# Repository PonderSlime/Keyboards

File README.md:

# Keyboards

A collection of all my personal keyboard projects.

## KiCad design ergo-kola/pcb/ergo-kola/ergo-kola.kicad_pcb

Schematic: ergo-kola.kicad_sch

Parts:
C1, C2, C3, C4, C5, C6, C7, C8, C9, C10, C11, C12, C13, C14, C15, C16, C17, C18, C19, C20, C21, C22, C23, C24, C25, C26, C27, C28, C29, C30, C31, C32, C33, C34, C35, C36, C37, C38, C39, C40, C41, C42, C43, C44, C45, C46, C47, C48, C49, C50, C51, C52: C 100uf; C_0805_2012Metric_Pad1.18x1.45mm_HandSolder
D1, D2, D3, D4, D5, D6, D7, D8, D9, D10, D11, D12, D13, D14, D15, D16, D17, D18, D19, D20, D21, D22, D23, D24, D25, D26, D27, D28, D29, D30, D31, D32, D33, D34, D35, D36, D37, D38, D39, D40, D41, D42, D43, D44, D45, D46, D47, D48, D49, D50, D51, D52: D; D_SOD-123
J1, J2: L_TRRS; PJ-320A
L1, L2, L3, L4, L5, L6, L7, L8, L9, L10, L11, L12, L13, L14, L15, L16, L17, L18, L19, L20, L21, L22, L23, L24, L25, L26, L27, L28, L29, L30, L31, L32, L33, L34, L35, L36, L37, L38, L39, L40, L41, L42, L43, L44, L45, L46, L47, L48, L49, L50, L51, L52: WS2812B; SK6812-MINI-E
SW1, SW2, SW3, SW4, SW5, SW6, SW7, SW8, SW9, SW10, SW11, SW12, SW13, SW14, SW15, SW16, SW17, SW18, SW19, SW20, SW21, SW22, SW23, SW24, SW25, SW26, SW27, SW28, SW29, SW30, SW31, SW32, SW33, SW34, SW35, SW36, SW37, SW38, SW39, SW40, SW41, SW42, SW43, SW44, SW45, SW46, SW47, SW48, SW49, SW50, SW51, SW52: CherryMX; CherryMX_1.00u_PCB_KailhSocket
U1, U2: Pico; RPi_Pico_SMD_TH

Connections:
GND: J1.1 (S), J2.1 (S), L1.3 (VSS), L2.3 (VSS), L3.3 (VSS), L4.3 (VSS), L5.3 (VSS), L6.3 (VSS), L7.3 (VSS), L8.3 (VSS), L9.3 (VSS), L10.3 (VSS), L11.3 (VSS), L12.3 (VSS), L13.3 (VSS), L14.3 (VSS), L15.3 (VSS), L16.3 (VSS), L17.3 (VSS), L18.3 (VSS), L19.3 (VSS), L20.3 (VSS), L21.3 (VSS), L22.3 (VSS), L23.3 (VSS), L24.3 (VSS), L25.3 (VSS), L26.3 (VSS), L27.3 (VSS), L28.3 (VSS), L29.3 (VSS), L30.3 (VSS), L31.3 (VSS), L32.3 (VSS), L33.3 (VSS), L34.3 (VSS), L35.3 (VSS), L36.3 (VSS), L37.3 (VSS), L38.3 (VSS), L39.3 (VSS), L40.3 (VSS), L41.3 (VSS), L42.3 (VSS), L43.3 (VSS), L44.3 (VSS), L45.3 (VSS), L46.3 (VSS), L47.3 (VSS), L48.3 (VSS), L49.3 (VSS), L50.3 (VSS), L51.3 (VSS), L52.3 (VSS), U1.3 (GND), U1.8 (GND), U1.13 (GND), U1.18 (GND), U1.23 (GND), U1.28 (GND), U1.38 (GND), U1.42 (GND), U2.3 (GND), U2.8 (GND), U2.13 (GND), U2.18 (GND), U2.23 (GND), U2.28 (GND), U2.38 (GND), U2.42 (GND)
L_C0: SW1.1, SW11.1, SW25.1, SW37.1, U1.10 (GPIO7)
L_C1: SW5.1, SW17.1, SW29.1, SW41.1, U1.11 (GPIO8)
L_C2: SW3.1, SW13.1, SW23.1, SW35.1, U1.12 (GPIO9)
L_C3: SW7.1, SW15.1, SW27.1, SW39.1, U1.14 (GPIO10)
L_C4: SW9.1, SW21.1, SW33.1, SW45.1, SW49.1, U1.15 (GPIO11)
L_C5: SW19.1, SW31.1, SW43.1, SW47.1, SW51.1, U1.16 (GPIO12)
L_R0: D1.1 (K), D3.1 (K), D5.1 (K), D7.1 (K), D9.1 (K), D19.1 (K), U1.27 (GPIO21)
L_R1: D11.1 (K), D13.1 (K), D15.1 (K), D17.1 (K), D21.1 (K), D31.1 (K), U1.26 (GPIO20)
L_R2: D23.1 (K), D25.1 (K), D27.1 (K), D29.1 (K), D33.1 (K), D43.1 (K), U1.25 (GPIO19)
L_R3: D35.1 (K), D37.1 (K), D39.1 (K), D41.1 (K), D45.1 (K), D47.1 (K), U1.24 (GPIO18)
L_R4: D49.1 (K), D51.1 (K), U1.22 (GPIO17)
L_RGB: L1.4 (DIN), U1.1 (GPIO0)
L_RX: J1.3 (R1), U1.7 (GPIO5_(RX))
L_TX: J1.4 (R2), U1.6 (GPIO4_(TX))
L_VBUS: C1.1, C11.1, C25.1, C37.1, C49.1, J1.2 (T), U1.40 (VBUS)
unnamed: D1.2 (A), SW1.2
unnamed: D2.2 (A), SW2.2
unnamed: D3.2 (A), SW3.2
unnamed: D4.2 (A), SW4.2
unnamed: D5.2 (A), SW5.2
unnamed: D6.2 (A), SW6.2
unnamed: D7.2 (A), SW7.2
unnamed: D8.2 (A), SW8.2
unnamed: D9.2 (A), SW9.2
unnamed: D10.2 (A), SW10.2
unnamed: D11.2 (A), SW11.2
unnamed: D12.2 (A), SW12.2
unnamed: D13.2 (A), SW13.2
unnamed: D14.2 (A), SW14.2
unnamed: D15.2 (A), SW15.2
unnamed: D16.2 (A), SW16.2
unnamed: D17.2 (A), SW17.2
unnamed: D18.2 (A), SW18.2
unnamed: D19.2 (A), SW19.2
unnamed: D20.2 (A), SW20.2
unnamed: D21.2 (A), SW21.2
unnamed: D22.2 (A), SW22.2
unnamed: D23.2 (A), SW23.2
unnamed: D24.2 (A), SW24.2
unnamed: D25.2 (A), SW25.2
unnamed: D26.2 (A), SW26.2
unnamed: D27.2 (A), SW27.2
unnamed: D28.2 (A), SW28.2
unnamed: D29.2 (A), SW29.2
unnamed: D30.2 (A), SW30.2
unnamed: D31.2 (A), SW31.2
unnamed: D32.2 (A), SW32.2
unnamed: D33.2 (A), SW33.2
unnamed: D34.2 (A), SW34.2
unnamed: D35.2 (A), SW35.2
unnamed: D36.2 (A), SW36.2
unnamed: D37.2 (A), SW37.2
unnamed: D38.2 (A), SW38.2
unnamed: D39.2 (A), SW39.2
unnamed: D40.2 (A), SW40.2
unnamed: D41.2 (A), SW41.2
unnamed: D42.2 (A), SW42.2
unnamed: D43.2 (A), SW43.2
unnamed: D44.2 (A), SW44.2
unnamed: D45.2 (A), SW45.2
unnamed: D46.2 (A), SW46.2
unnamed: D47.2 (A), SW47.2
unnamed: D48.2 (A), SW48.2
unnamed: D49.2 (A), SW49.2
unnamed: D50.2 (A), SW50.2
unnamed: D51.2 (A), SW51.2
unnamed: D52.2 (A), SW52.2
unnamed: L1.2 (DOUT), L5.4 (DIN)
unnamed: C1.2, C5.1, L1.1 (VDD)
unnamed: L2.4 (DIN), L6.2 (DOUT)
unnamed: L2.2 (DOUT), L32.4 (DIN)
unnamed: C2.2, L2.1 (VDD)
unnamed: L3.4 (DIN), L5.2 (DOUT)
unnamed: L3.2 (DOUT), L7.4 (DIN)
unnamed: C3.2, C7.1, L3.1 (VDD)
unnamed: L4.4 (DIN), L8.2 (DOUT)
unnamed: L4.2 (DOUT), L6.4 (DIN)
unnamed: C4.2, C6.1, L4.1 (VDD)
unnamed: C3.1, C5.2, L5.1 (VDD)
unnamed: C2.1, C6.2, L6.1 (VDD)
unnamed: L7.2 (DOUT), L9.4 (DIN)
unnamed: C7.2, C9.1, L7.1 (VDD)
unnamed: C4.1, C8.2, L8.1 (VDD)
unnamed: C9.2, C19.1, L9.1 (VDD)
unnamed: L10.4 (DIN), L20.2 (DOUT)
unnamed: L8.4 (DIN), L10.2 (DOUT)
unnamed: C8.1, C10.2, L10.1 (VDD)
unnamed: L11.4 (DIN), L19.2 (DOUT)
unnamed: L11.2 (DOUT), L17.4 (DIN)
unnamed: C11.2, C17.1, L11.1 (VDD)
unnamed: L12.4 (DIN), L18.2 (DOUT)
unnamed: L12.2 (DOUT), L44.4 (DIN)
unnamed: C12.2, L12.1 (VDD)
unnamed: L13.4 (DIN), L17.2 (DOUT)
unnamed: L13.2 (DOUT), L15.4 (DIN)
unnamed: C13.2, C15.1, L13.1 (VDD)
unnamed: L14.4 (DIN), L16.2 (DOUT)
unnamed: L14.2 (DOUT), L18.4 (DIN)
unnamed: C14.2, C18.1, L14.1 (VDD)
unnamed: L15.2 (DOUT), L21.4 (DIN)
unnamed: C15.2, C21.1, L15.1 (VDD)
unnamed: L16.4 (DIN), L22.2 (DOUT)
unnamed: C14.1, C16.2, L16.1 (VDD)
unnamed: C13.1, C17.2, L17.1 (VDD)
unnamed: C12.1, C18.2, L18.1 (VDD)
unnamed: L9.2 (DOUT), L19.4 (DIN)
unnamed: C19.2, L19.1 (VDD)
unnamed: C10.1, C20.2, L20.1 (VDD)
unnamed: L21.2 (DOUT), L31.4 (DIN)
unnamed: C21.2, C31.1, L21.1 (VDD)
unnamed: L22.4 (DIN), L32.2 (DOUT)
unnamed: C16.1, C22.2, L22.1 (VDD)
unnamed: L23.4 (DIN), L29.2 (DOUT)
unnamed: L23.2 (DOUT), L27.4 (DIN)
unnamed: C23.2, C27.1, L23.1 (VDD)
unnamed: L24.4 (DIN), L28.2 (DOUT)
unnamed: L24.2 (DOUT), L30.4 (DIN)
unnamed: C24.2, C30.1, L24.1 (VDD)
unnamed: L25.4 (DIN), L31.2 (DOUT)
unnamed: L25.2 (DOUT), L29.4 (DIN)
unnamed: C25.2, C29.1, L25.1 (VDD)
unnamed: L26.4 (DIN), L30.2 (DOUT)
unnamed: L26.2 (DOUT), L48.4 (DIN)
unnamed: C26.2, L26.1 (VDD)
unnamed: L27.2 (DOUT), L33.4 (DIN)
unnamed: C27.2, C33.1, L27.1 (VDD)
unnamed: L28.4 (DIN), L34.2 (DOUT)
unnamed: C24.1, C28.2, L28.1 (VDD)
unnamed: C23.1, C29.2, L29.1 (VDD)
unnamed: C26.1, C30.2, L30.1 (VDD)
unnamed: C31.2, L31.1 (VDD)
unnamed: C22.1, C32.2, L32.1 (VDD)
unnamed: L33.2 (DOUT), L43.4 (DIN)
unnamed: C33.2, C43.1, L33.1 (VDD)
unnamed: L34.4 (DIN), L44.2 (DOUT)
unnamed: C28.1, C34.2, L34.1 (VDD)
unnamed: L35.4 (DIN), L41.2 (DOUT)
unnamed: L35.2 (DOUT), L39.4 (DIN)
unnamed: C35.2, C39.1, L35.1 (VDD)
unnamed: L36.4 (DIN), L40.2 (DOUT)
unnamed: L36.2 (DOUT), L42.4 (DIN)
unnamed: C36.2, C42.1, L36.1 (VDD)
unnamed: L37.4 (DIN), L43.2 (DOUT)
unnamed: L37.2 (DOUT), L41.4 (DIN)
unnamed: C37.2, C41.1, L37.1 (VDD)
unnamed: L38.4 (DIN), L42.2 (DOUT)
unnamed: L38.2 (DOUT), L52.4 (DIN)
unnamed: C38.2, L38.1 (VDD)
unnamed: L39.2 (DOUT), L45.4 (DIN)
unnamed: C39.2, C45.1, L39.1 (VDD)
unnamed: L40.4 (DIN), L46.2 (DOUT)
unnamed: C36.1, C40.2, L40.1 (VDD)
unnamed: C35.1, C41.2, L41.1 (VDD)
unnamed: C38.1, C42.2, L42.1 (VDD)
unnamed: C43.2, L43.1 (VDD)
unnamed: C34.1, C44.2, L44.1 (VDD)
unnamed: L45.2 (DOUT), L47.4 (DIN)
unnamed: C45.2, C47.1, L45.1 (VDD)
unnamed: L46.4 (DIN), L48.2 (DOUT)
unnamed: C40.1, C46.2, L46.1 (VDD)
unnamed: L47.2 (DOUT), L49.4 (DIN)
unnamed: C47.2, L47.1 (VDD)
unnamed: C46.1, C48.2, L48.1 (VDD)
unnamed: L49.2 (DOUT), L51.4 (DIN)
unnamed: C49.2, C51.1, L49.1 (VDD)
unnamed: L50.4 (DIN), L52.2 (DOUT)
unnamed: C50.2, L50.1 (VDD)
unnamed: C51.2, L51.1 (VDD)
unnamed: C50.1, C52.2, L52.1 (VDD)
R_C6: SW20.1, SW32.1, SW44.1, SW48.1, SW52.1, U2.9 (GPIO6)
R_C7: SW10.1, SW22.1, SW34.1, SW46.1, SW50.1, U2.10 (GPIO7)
R_C8: SW8.1, SW16.1, SW28.1, SW40.1, U2.11 (GPIO8)
R_C9: SW4.1, SW14.1, SW24.1, SW36.1, U2.12 (GPIO9)
R_C10: SW6.1, SW18.1, SW30.1, SW42.1, U2.14 (GPIO10)
R_C11: SW2.1, SW12.1, SW26.1, SW38.1, U2.15 (GPIO11)
R_C12: U2.16 (GPIO12)
R_R0: D2.1 (K), D4.1 (K), D6.1 (K), D8.1 (K), D10.1 (K), D20.1 (K), U2.27 (GPIO21)
R_R1: D12.1 (K), D14.1 (K), D16.1 (K), D18.1 (K), D22.1 (K), D32.1 (K), U2.26 (GPIO20)
R_R2: D24.1 (K), D26.1 (K), D28.1 (K), D30.1 (K), D34.1 (K), D44.1 (K), U2.25 (GPIO19)
R_R3: D36.1 (K), D38.1 (K), D40.1 (K), D42.1 (K), D46.1 (K), D48.1 (K), U2.24 (GPIO18)
R_R4: D50.1 (K), D52.1 (K), U2.22 (GPIO17)
R_RGB: L20.4 (DIN), U2.1 (GPIO0)
R_RX: J2.4 (R2), U2.7 (GPIO5_(RX))
R_TX: J2.3 (R1), U2.6 (GPIO4_(TX))
R_VBUS: C20.1, C32.1, C44.1, C48.1, C52.1, J2.2 (T), U2.40 (VBUS)

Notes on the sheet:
TRRS Cable
Encoder
MX Switch Matrix
Per-Key RGB Lighting
Use PJ-320A TRRS Jack for this
Use an EC12 Encoder, with a varying height for the cap to get it to the preferred height
Use SK6812MINI-E LEDs or similar for this
use these 100 uf capacitors:
Use standard Kailh Hotswap Sockets (And Cherry MX Reds) Probably use Durock stabalizers for this too Also, 1N4148W Diodes
https://www.mouser.com/ProductDetail/Samsung-Electro-Mechanics/CL21A107MQYNNWE?qs=sGAEpiMZZMsh%252B1woXyUXj7hTFrnMyX907rJbWHkejgM%3D

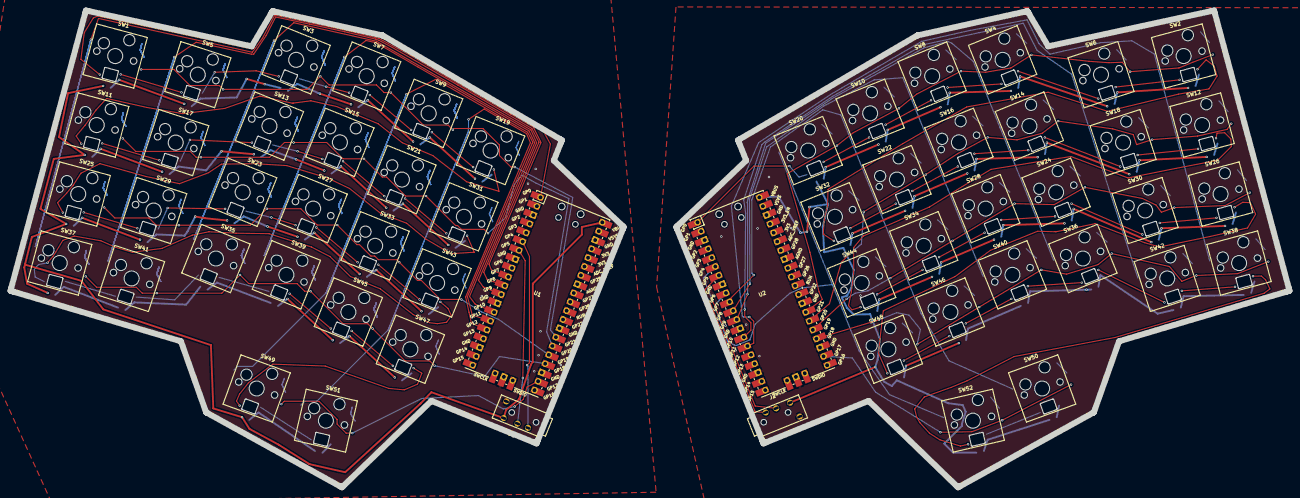
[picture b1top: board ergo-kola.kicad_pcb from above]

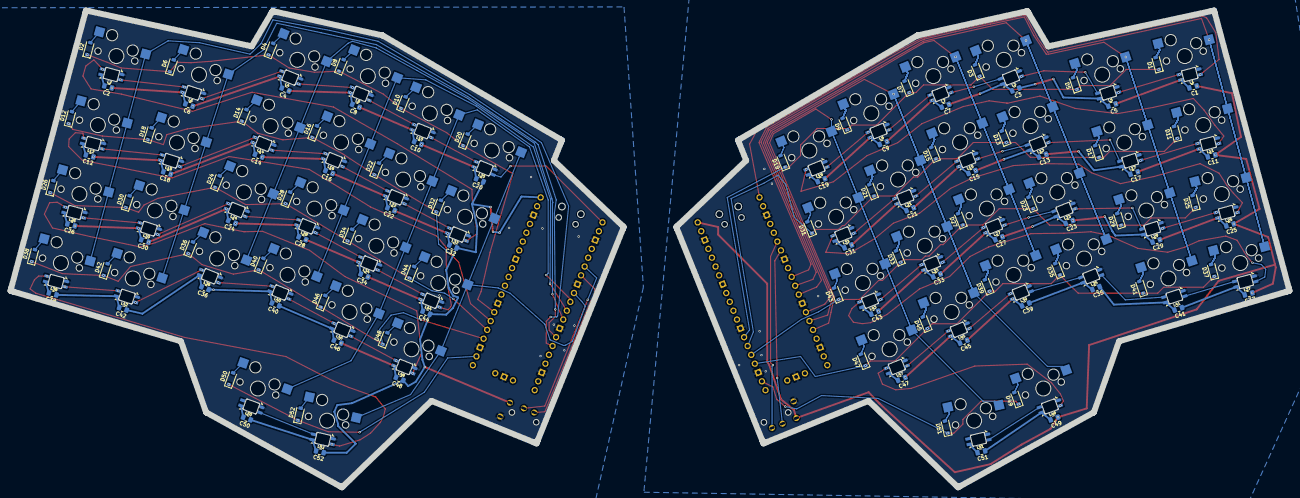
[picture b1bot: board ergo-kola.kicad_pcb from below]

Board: 2 copper layers, 341.1 x 127.2 mm, 212 parts (156 on the bottom side), 185 nets.

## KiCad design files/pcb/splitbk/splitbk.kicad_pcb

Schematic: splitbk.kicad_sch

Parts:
D1, D2, D3, D4, D5, D6, D7, D8, D9, D10, D11, D12, D13, D14, D15, D16, D17, D18, D19, D20, D21, D22, D23, D24, D25, D26, D27, D28, D29, D30, D31, D32, D33, D34, D35, D36, D37, D38, D39, D40, D41, D42, D43, D44, D45, D46, D47, D48, D49, D50, D51, D52, D53, D54, D55, D56, D57, D58, D59: D; D_SOD-123
D1.5, D2.5, D3.5, D4.5, D5.5, D6.5, D7.5, D8.5, D9.5, D10.5, D11.5, D12.5, D13.5, D14.5, D15.5, D16.5, D17.5, D18.5, D19.5, D20.5, D21.5, D22.5, D23.5, D24.5, D25.5, D26.5, D27.5, D28.5, D29.5, D30.5, D31.5, D35.5, D36.5, D37.5, D38.5, D39.5, D40.5, D41.5, D42.5, D43.5, D44.5, D45.5, D46.5, D47.5, D48.5, D49.5, D50.5, D51.5, D52.5, D53.5, D54.5, D55.5, D56.5, D57.5, D58.5, D59.5, D60.5, D61.5, D62.5, D63.5, D64.5: WS2812B; SK6812-MINI-E
J1, J2: L_TRRS; PJ-320A
SW1, SW2, SW3, SW4, SW5, SW6, SW7, SW8, SW9, SW10, SW11, SW12, SW14, SW15, SW16, SW17, SW18, SW19, SW20, SW21, SW22, SW23, SW24, SW25, SW26, SW27, SW28, SW29, SW30, SW31, SW32, SW33, SW34, SW35, SW36, SW37, SW38, SW39, SW40, SW41, SW43, SW44, SW45, SW46, SW47, SW48, SW49, SW50, SW51, SW52: CherryMX; CherryMX_1.00u_PCB_KailhSocket
SW13: CherryMX; CherryMX_2.00u_PCB_KailhSocket_StabWireBottom
SW42, SW53: RotaryEncoder; RotaryEncoder_Alps_EC12E_Vertical_H20mm
SW54, SW61: CherryMX; CherryMX_2.25u_PCB_KailhSocket_StabWireBottom
SW55, SW60: CherryMX; CherryMX_1.50u_PCB_KailhSocket
SW56, SW59: CherryMX; CherryMX_1.25u_PCB_KailhSocket
SW57, SW58: CherryMX; CherryMX_2.75u_PCB_KailhSocket_StabWireBottom
U1, U2: Pico; RPi_Pico_SMD_TH

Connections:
GND: D1.5.3 (VSS), D2.5.3 (VSS), D3.5.3 (VSS), D4.5.3 (VSS), D5.5.3 (VSS), D6.5.3 (VSS), D7.5.3 (VSS), D8.5.3 (VSS), D9.5.3 (VSS), D10.5.3 (VSS), D11.5.3 (VSS), D12.5.3 (VSS), D13.5.3 (VSS), D14.5.3 (VSS), D15.5.3 (VSS), D16.5.3 (VSS), D17.5.3 (VSS), D18.5.3 (VSS), D19.5.3 (VSS), D20.5.3 (VSS), D21.5.3 (VSS), D22.5.3 (VSS), D23.5.3 (VSS), D24.5.3 (VSS), D25.5.3 (VSS), D26.5.3 (VSS), D27.5.3 (VSS), D28.5.3 (VSS), D29.5.3 (VSS), D30.5.3 (VSS), D31.5.3 (VSS), D35.5.3 (VSS), D36.5.3 (VSS), D37.5.3 (VSS), D38.5.3 (VSS), D39.5.3 (VSS), D40.5.3 (VSS), D41.5.3 (VSS), D42.5.3 (VSS), D43.5.3 (VSS), D44.5.3 (VSS), D45.5.3 (VSS), D46.5.3 (VSS), D47.5.3 (VSS), D48.5.3 (VSS), D49.5.3 (VSS), D50.5.3 (VSS), D51.5.3 (VSS), D52.5.3 (VSS), D53.5.3 (VSS), D54.5.3 (VSS), D55.5.3 (VSS), D56.5.3 (VSS), D57.5.3 (VSS), D58.5.3 (VSS), D59.5.3 (VSS), D60.5.3 (VSS), D61.5.3 (VSS), D62.5.3 (VSS), D63.5.3 (VSS), D64.5.3 (VSS), J1.1 (S), J2.1 (S), SW42.C, SW42.MP, SW53.C, SW53.MP, U1.3 (GND), U1.8 (GND), U1.13 (GND), U1.18 (GND), U1.23 (GND), U1.28 (GND), U1.38 (GND), U2.3 (GND), U2.8 (GND), U2.13 (GND), U2.18 (GND), U2.23 (GND), U2.28 (GND), U2.38 (GND), U2.42 (GND)
L_C0: SW1.1, SW14.1, SW28.1, U1.10 (GPIO7)
L_C1: SW2.1, SW15.1, SW29.1, U1.11 (GPIO8)
L_C2: SW3.1, SW16.1, SW30.1, SW43.1, SW54.1, U1.12 (GPIO9)
L_C3: SW4.1, SW17.1, SW31.1, SW44.1, SW55.1, U1.14 (GPIO10)
L_C4: SW5.1, SW18.1, SW32.1, SW45.1, SW56.1, U1.15 (GPIO11)
L_C5: SW6.1, SW19.1, SW33.1, SW46.1, SW57.1, U1.16 (GPIO12)
L_C6: SW7.1, SW20.1, SW34.1, SW47.1, U1.17 (GPIO13)
L_ECA: SW42.A, U1.27 (GPIO21)
L_ECB: SW42.B, U1.26 (GPIO20)
L_GND: U1.42 (GND)
L_GP0: J1.4 (R2), U1.1 (GPIO0)
L_GP1: J1.3 (R1), U1.2 (GPIO1)
L_R0: D1.1 (K), D2.1 (K), D3.1 (K), D4.1 (K), D5.1 (K), D6.1 (K), D7.1 (K), U1.4 (GPIO2)
L_R1: D8.1 (K), D9.1 (K), D10.1 (K), D11.1 (K), D12.1 (K), D13.1 (K), D14.1 (K), U1.5 (GPIO3)
L_R2: D15.1 (K), D16.1 (K), D17.1 (K), D18.1 (K), D19.1 (K), D20.1 (K), D21.1 (K), U1.6 (GPIO4)
L_R3: D22.1 (K), D23.1 (K), D24.1 (K), D25.1 (K), D26.1 (K), U1.7 (GPIO5)
L_R4: D27.1 (K), D28.1 (K), D29.1 (K), D30.1 (K), U1.9 (GPIO6)
L_RGB: D1.5.4 (DIN), U1.20 (GPIO15)
L_VBUS: D1.5.1 (VDD), D2.5.1 (VDD), D3.5.1 (VDD), D4.5.1 (VDD), D5.5.1 (VDD), D6.5.1 (VDD), D7.5.1 (VDD), D8.5.1 (VDD), D9.5.1 (VDD), D10.5.1 (VDD), D11.5.1 (VDD), D12.5.1 (VDD), D13.5.1 (VDD), D14.5.1 (VDD), D15.5.1 (VDD), D16.5.1 (VDD), D17.5.1 (VDD), D18.5.1 (VDD), D19.5.1 (VDD), D20.5.1 (VDD), D21.5.1 (VDD), D22.5.1 (VDD), D23.5.1 (VDD), D24.5.1 (VDD), D25.5.1 (VDD), D26.5.1 (VDD), D27.5.1 (VDD), D28.5.1 (VDD), D29.5.1 (VDD), D30.5.1 (VDD), D31.5.1 (VDD), J1.2 (T), U1.40 (VBUS)
unnamed: D1.2 (A), SW1.2
unnamed: D1.5.2 (DOUT), D2.5.4 (DIN)
unnamed: D2.2 (A), SW2.2
unnamed: D2.5.2 (DOUT), D3.5.4 (DIN)
unnamed: D3.2 (A), SW3.2
unnamed: D3.5.2 (DOUT), D4.5.4 (DIN)
unnamed: D4.2 (A), SW4.2
unnamed: D4.5.2 (DOUT), D5.5.4 (DIN)
unnamed: D5.2 (A), SW5.2
unnamed: D5.5.2 (DOUT), D6.5.4 (DIN)
unnamed: D6.2 (A), SW6.2
unnamed: D6.5.2 (DOUT), D7.5.4 (DIN)
unnamed: D7.2 (A), SW7.2
unnamed: D7.5.2 (DOUT), D8.5.4 (DIN)
unnamed: D8.2 (A), SW14.2
unnamed: D8.5.2 (DOUT), D9.5.4 (DIN)
unnamed: D9.2 (A), SW15.2
unnamed: D10.2 (A), SW16.2
unnamed: D9.5.2 (DOUT), D10.5.4 (DIN)
unnamed: D10.5.2 (DOUT), D11.5.4 (DIN)
unnamed: D11.2 (A), SW17.2
unnamed: D11.5.2 (DOUT), D12.5.4 (DIN)
unnamed: D12.2 (A), SW18.2
unnamed: D12.5.2 (DOUT), D13.5.4 (DIN)
unnamed: D13.2 (A), SW19.2
unnamed: D13.5.2 (DOUT), D14.5.4 (DIN)
unnamed: D14.2 (A), SW20.2
unnamed: D14.5.2 (DOUT), D15.5.4 (DIN)
unnamed: D15.2 (A), SW28.2
unnamed: D15.5.2 (DOUT), D16.5.4 (DIN)
unnamed: D16.2 (A), SW29.2
unnamed: D16.5.2 (DOUT), D17.5.4 (DIN)
unnamed: D17.2 (A), SW30.2
unnamed: D17.5.2 (DOUT), D18.5.4 (DIN)
unnamed: D18.2 (A), SW31.2
unnamed: D18.5.2 (DOUT), D19.5.4 (DIN)
unnamed: D19.2 (A), SW32.2
unnamed: D19.5.2 (DOUT), D20.5.4 (DIN)
unnamed: D20.2 (A), SW33.2
unnamed: D20.5.2 (DOUT), D21.5.4 (DIN)
unnamed: D21.2 (A), SW34.2
unnamed: D21.5.2 (DOUT), D22.5.4 (DIN)
unnamed: D22.2 (A), SW43.2
unnamed: D22.5.2 (DOUT), D23.5.4 (DIN)
unnamed: D23.2 (A), SW44.2
unnamed: D23.5.2 (DOUT), D24.5.4 (DIN)
unnamed: D24.2 (A), SW45.2
unnamed: D24.5.2 (DOUT), D25.5.4 (DIN)
unnamed: D25.2 (A), SW46.2
unnamed: D25.5.2 (DOUT), D26.5.4 (DIN)
unnamed: D26.2 (A), SW47.2
unnamed: D26.5.2 (DOUT), D27.5.4 (DIN)
unnamed: D27.2 (A), SW54.2
unnamed: D27.5.2 (DOUT), D28.5.4 (DIN)
unnamed: D28.2 (A), SW55.2
unnamed: D28.5.2 (DOUT), D29.5.4 (DIN)
unnamed: D29.2 (A), SW56.2
unnamed: D29.5.2 (DOUT), D30.5.4 (DIN)
unnamed: D30.2 (A), SW57.2
unnamed: D30.5.2 (DOUT), D31.5.4 (DIN)
unnamed: D31.2 (A), SW8.2
unnamed: D32.2 (A), SW9.2
unnamed: D33.2 (A), SW10.2
unnamed: D34.2 (A), SW11.2
unnamed: D35.2 (A), SW12.2
unnamed: D35.5.2 (DOUT), D36.5.4 (DIN)
unnamed: D36.2 (A), SW13.2
unnamed: D36.5.2 (DOUT), D37.5.4 (DIN)
unnamed: D37.2 (A), SW21.2
unnamed: D37.5.2 (DOUT), D38.5.4 (DIN)
unnamed: D38.2 (A), SW22.2
unnamed: D38.5.2 (DOUT), D39.5.4 (DIN)
unnamed: D39.2 (A), SW23.2
unnamed: D39.5.2 (DOUT), D40.5.4 (DIN)
unnamed: D40.2 (A), SW24.2
unnamed: D40.5.2 (DOUT), D41.5.4 (DIN)
unnamed: D41.2 (A), SW25.2
unnamed: D41.5.2 (DOUT), D42.5.4 (DIN)
unnamed: D42.2 (A), SW26.2
unnamed: D42.5.2 (DOUT), D43.5.4 (DIN)
unnamed: D43.2 (A), SW27.2
unnamed: D43.5.2 (DOUT), D44.5.4 (DIN)
unnamed: D44.2 (A), SW35.2
unnamed: D44.5.2 (DOUT), D45.5.4 (DIN)
unnamed: D45.2 (A), SW36.2
unnamed: D45.5.2 (DOUT), D46.5.4 (DIN)
unnamed: D46.2 (A), SW37.2
unnamed: D46.5.2 (DOUT), D47.5.4 (DIN)
unnamed: D47.2 (A), SW38.2
unnamed: D47.5.2 (DOUT), D48.5.4 (DIN)
unnamed: D48.2 (A), SW39.2
unnamed: D48.5.2 (DOUT), D49.5.4 (DIN)
unnamed: D49.2 (A), SW40.2
unnamed: D49.5.2 (DOUT), D50.5.4 (DIN)
unnamed: D50.2 (A), SW41.2
unnamed: D50.5.2 (DOUT), D51.5.4 (DIN)
unnamed: D51.2 (A), SW48.2
unnamed: D51.5.2 (DOUT), D52.5.4 (DIN)
unnamed: D52.2 (A), SW49.2
unnamed: D52.5.2 (DOUT), D53.5.4 (DIN)
unnamed: D53.2 (A), SW50.2
unnamed: D53.5.2 (DOUT), D54.5.4 (DIN)
unnamed: D54.2 (A), SW51.2
unnamed: D54.5.2 (DOUT), D55.5.4 (DIN)
unnamed: D55.2 (A), SW52.2
unnamed: D55.5.2 (DOUT), D56.5.4 (DIN)
unnamed: D56.2 (A), SW58.2
unnamed: D56.5.2 (DOUT), D57.5.4 (DIN)
unnamed: D57.2 (A), SW59.2
unnamed: D57.5.2 (DOUT), D58.5.4 (DIN)
unnamed: D58.2 (A), SW60.2
unnamed: D58.5.2 (DOUT), D59.5.4 (DIN)
unnamed: D59.2 (A), SW61.2
unnamed: D59.5.2 (DOUT), D60.5.4 (DIN)
unnamed: D60.5.2 (DOUT), D61.5.4 (DIN)
unnamed: D61.5.2 (DOUT), D62.5.4 (DIN)
unnamed: D62.5.2 (DOUT), D63.5.4 (DIN)
unnamed: D63.5.2 (DOUT), D64.5.4 (DIN)
R_C7: SW8.1, SW21.1, SW35.1, SW48.1, U2.10 (GPIO7)
R_C8: SW9.1, SW22.1, SW36.1, SW49.1, SW58.1, U2.11 (GPIO8)
R_C9: SW10.1, SW23.1, SW37.1, SW50.1, SW59.1, U2.12 (GPIO9)
R_C10: SW11.1, SW24.1, SW38.1, SW51.1, SW60.1, U2.14 (GPIO10)
R_C11: SW12.1, SW25.1, SW39.1, SW52.1, SW61.1, U2.15 (GPIO11)
R_C12: SW13.1, SW26.1, SW40.1, U2.16 (GPIO12)
R_C13: SW27.1, SW41.1, U2.17 (GPIO13)
R_ECA: SW53.A, U2.27 (GPIO21)
R_ECB: SW53.B, U2.26 (GPIO20)
R_GP0: J2.4 (R2), U2.1 (GPIO0)
R_GP1: J2.3 (R1), U2.2 (GPIO1)
R_R0: D31.1 (K), D32.1 (K), D33.1 (K), D34.1 (K), D35.1 (K), D36.1 (K), U2.4 (GPIO2)
R_R1: D37.1 (K), D38.1 (K), D39.1 (K), D40.1 (K), D41.1 (K), D42.1 (K), D43.1 (K), U2.5 (GPIO3)
R_R2: D44.1 (K), D45.1 (K), D46.1 (K), D47.1 (K), D48.1 (K), D49.1 (K), D50.1 (K), U2.6 (GPIO4)
R_R3: D51.1 (K), D52.1 (K), D53.1 (K), D54.1 (K), D55.1 (K), U2.7 (GPIO5)
R_R4: D56.1 (K), D57.1 (K), D58.1 (K), D59.1 (K), U2.9 (GPIO6)
R_VBUS: D35.5.1 (VDD), D36.5.1 (VDD), D37.5.1 (VDD), D38.5.1 (VDD), D39.5.1 (VDD), D40.5.1 (VDD), D41.5.1 (VDD), D42.5.1 (VDD), D43.5.1 (VDD), D44.5.1 (VDD), D45.5.1 (VDD), D46.5.1 (VDD), D47.5.1 (VDD), D48.5.1 (VDD), D49.5.1 (VDD), D50.5.1 (VDD), D51.5.1 (VDD), D52.5.1 (VDD), D53.5.1 (VDD), D54.5.1 (VDD), D55.5.1 (VDD), D56.5.1 (VDD), D57.5.1 (VDD), D58.5.1 (VDD), D59.5.1 (VDD), D60.5.1 (VDD), D61.5.1 (VDD), D62.5.1 (VDD), D63.5.1 (VDD), D64.5.1 (VDD), J2.2 (T), U2.40 (VBUS)

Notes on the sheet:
TRRS Cable
Encoder
MX Switch Matrix
Per-Key RGB Lighting
Use PJ-320A TRRS Jack for this
Use an EC12 Encoder, with a varying height for the cap to get it to the preferred height
Use SK6812MINI-E LEDs or similar for this
Use standard Kailh Hotswap Sockets (And Cherry MX Reds) Probably use Durock stabalizers for this too Also, 1N4148W Diodes

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
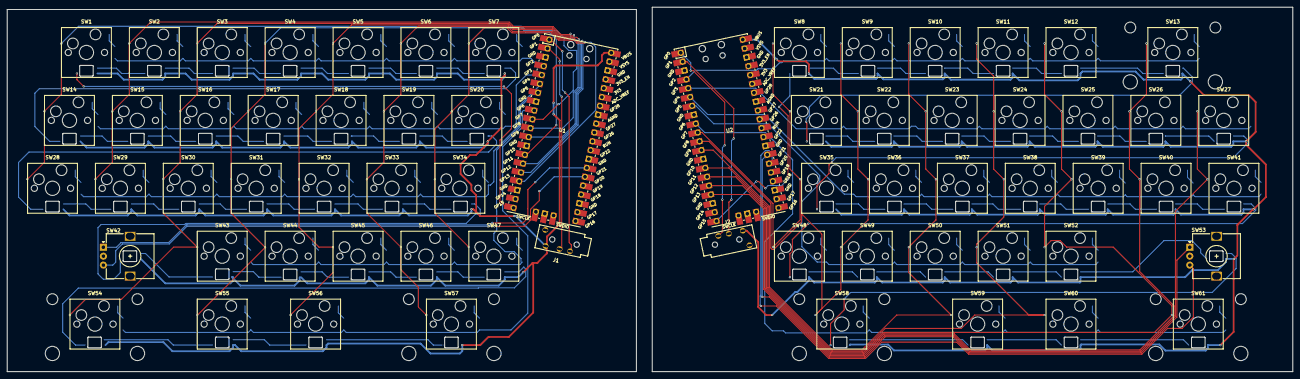
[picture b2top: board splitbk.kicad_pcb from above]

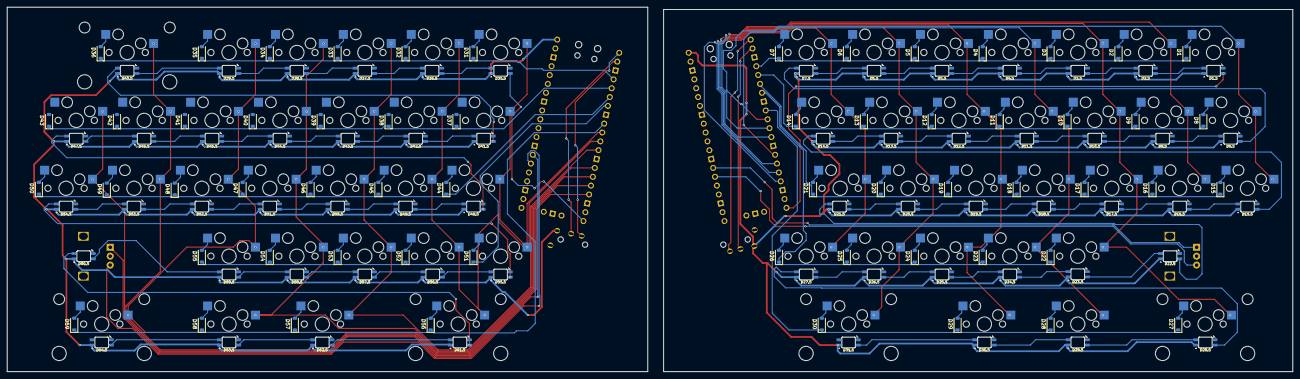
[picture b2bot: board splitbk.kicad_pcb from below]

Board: 2 copper layers, 360.7 x 102.2 mm, 185 parts (120 on the bottom side), 155 nets.

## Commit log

2025-02-22 Pcb half done!
2025-02-22 All rows wired, Moving onto rightside LED placement
2025-02-22 PCB Routing Completed
2025-02-23 Rebranded the keyboard! :)
2025-02-23 Finished rebranding, added 3d model!
2025-02-24 Added the firmware, added base plate file template + Reference model
2025-02-24 Changed keymap.c to be a little more readable
2025-02-25 Added the case files, Compiled firmware, Hopefully works
2025-02-25 Added branding to the case, and added pictures
2025-02-25 Added assets to readme
2025-02-25 last commit was for wrong repo...
2025-02-25 Fixed typo...
2025-02-25 Added gitignore to subfolder for ease when copying
2025-02-25 Added branding to pcb
2025-03-01 forgot to commit some stuff
2025-03-13 Started Ergo-Kola Keyboard
2025-03-13 Autolayout did not work (experiment), manually doing it via spreadsheet
2025-03-15 PCB Done!
2025-03-15 Finished PCB and Case!
2025-03-15 Fixed an oopsie mistake
2025-03-16 Neopixels power fixed
2025-03-17 Moved folders of stuff
2025-03-17 Added bill of materials for ergo-kola
2025-03-17 Organized BOM
2025-03-17 Updated readme of ergo-kola
2025-06-06 Added Ergo-Kola BOM
2025-09-10 Added ergo-kola output, retro-70-kb git submodule added
2025-10-06 Update README.md
    Added Onshape Link to README.md
2025-10-06 Update README.md
    Added TRRS Cable to BOM
2025-10-06 Update BOM.csv
    Added TRRS Cable to BOM
2025-10-06 Fixed issues with URLs
2025-10-06 Update README.md
    Fixed BOM URLs again
2025-10-06 Update README.md
    Fully fixed MarkDown BOM
2025-10-06 Update BOM.csv
    Added pricing to BOM.csv
2025-10-06 Update README.md
    Added total price to BOM
2025-10-06 Update README.md
    Removed SplitKB from the ordering stuff to cut costs on shipping
2025-10-06 Update BOM.csv
    Removed SplitKB.com from the BOM
2025-10-09 Update README.md
    Added keycaps to price, fixed other issues with costs in BOM (now $145 dollars :/ )
2025-10-09 Update BOM.csv
    Syncronized with BOM in README.md
2025-10-09 Split board files in two, exported both sides for production
2025-10-11 Update README.md
    Added Tariffs ('merica :c )
2025-10-11 Update BOM.csv
    Added tariffs ('merica >:c )
